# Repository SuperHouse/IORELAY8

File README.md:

I/O Breakout To 8 Relay Drivers
===============================
Copyright 2017-2019 SuperHouse Pty Ltd  
SuperHouse site:  www.superhouse.tv  

Breaks out a 2x6 pin header to 8 low-side MOSFETs suitable for switching
loads such as relays.

Features:

 * Inputs from both a 2x6 shrouded header and separate solder pads

More information is available at:

  http://www.superhouse.tv/iorelay8

INSTALLATION
------------
The design is saved as an EAGLE project. EAGLE PCB design software is
available from www.cadsoftusa.com free for non-commercial use. To use
this project download it and place the directory containing these files
into the "eagle" directory on your computer. Then open EAGLE and
navigate to the project.

DISTRIBUTION
------------
The specific terms of distribution of this project are governed by the
license referenced below.

LICENSE
-------
Licensed under the TAPR Open Hardware License (www.tapr.org/OHL).
The "license" folder within this repository also contains a copy of
this license in plain text format.

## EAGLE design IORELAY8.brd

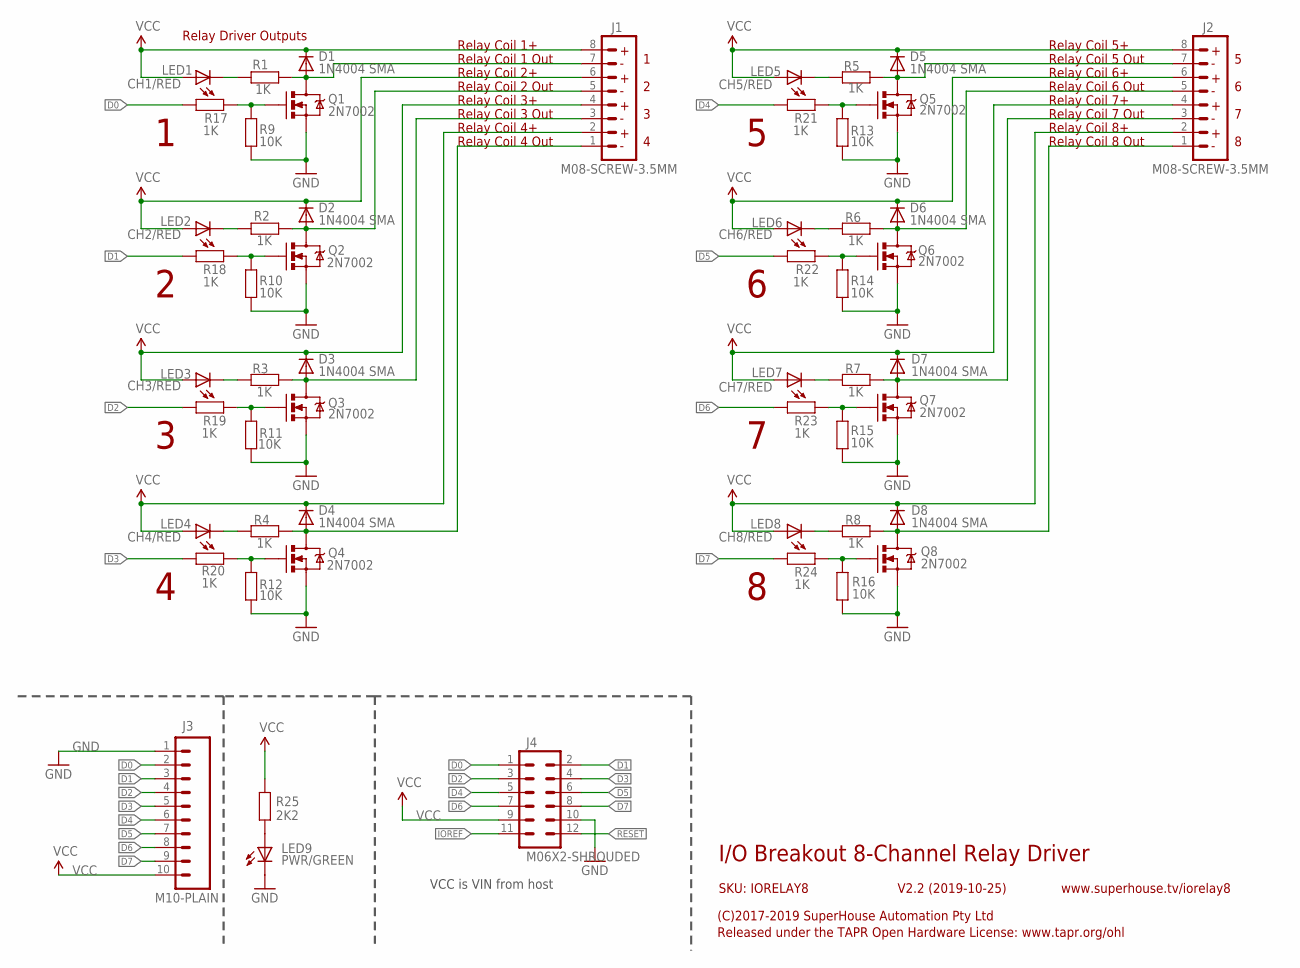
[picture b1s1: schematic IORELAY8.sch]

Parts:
D1, D2, D3, D4, D5, D6, D7, D8: 1N4004 SMA; SMA-DIODE
J1, J2: M08-SCREW-3.5MM; SCREWTERMINAL_3.5MM_8
J3: M10-PLAIN; 1X10
J4: M06X2-SHROUDED; 2X6-SHROUDED
LED1: CH1/RED; LED-0603
LED2: CH2/RED; LED-0603
LED3: CH3/RED; LED-0603
LED4: CH4/RED; LED-0603
LED5: CH5/RED; LED-0603
LED6: CH6/RED; LED-0603
LED7: CH7/RED; LED-0603
LED8: CH8/RED; LED-0603
LED9: PWR/GREEN; LED-0603
Q1, Q2, Q3, Q4, Q5, Q6, Q7, Q8: 2N7002; SOT23-3
R1, R2, R3, R4, R5, R6, R7, R8, R17, R18, R19, R20, R21, R22, R23, R24: 1K; R0603
R9, R10, R11, R12, R13, R14, R15, R16: 10K; R0603
R25: 2K2; R0603

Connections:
D0: J3.2, J4.1, R17.2
D1: J3.3, J4.2, R18.2
D2: J3.4, J4.3, R19.2
D3: J3.5, J4.4, R20.2
D4: J3.6, J4.5, R21.2
D5: J3.7, J4.6, R22.2
D6: J3.8, J4.7, R23.2
D7: J3.9, J4.8, R24.2
GND: J3.1, J4.10, LED9.C, Q1.2 (S), Q2.2 (S), Q3.2 (S), Q4.2 (S), Q5.2 (S), Q6.2 (S), Q7.2 (S), Q8.2 (S), R9.1, R10.1, R11.1, R12.1, R13.1, R14.1, R15.1, R16.1
IOREF: J4.11
unnamed: Q1.1 (G), R9.2, R17.1
unnamed: D2.A, J1.5, Q2.3 (D), R2.2
unnamed: LED9.A, R25.1
unnamed: D1.A, J1.7, Q1.3 (D), R1.2
unnamed: Q2.1 (G), R10.2, R18.1
unnamed: D3.A, J1.3, Q3.3 (D), R3.2
unnamed: Q3.1 (G), R11.2, R19.1
unnamed: D4.A, J1.1, Q4.3 (D), R4.2
unnamed: Q4.1 (G), R12.2, R20.1
unnamed: D5.A, J2.7, Q5.3 (D), R5.2
unnamed: Q5.1 (G), R13.2, R21.1
unnamed: D6.A, J2.5, Q6.3 (D), R6.2
unnamed: Q6.1 (G), R14.2, R22.1
unnamed: D7.A, J2.3, Q7.3 (D), R7.2
unnamed: Q7.1 (G), R15.2, R23.1
unnamed: D8.A, J2.1, Q8.3 (D), R8.2
unnamed: Q8.1 (G), R16.2, R24.1
unnamed: LED2.C, R2.1
unnamed: LED4.C, R4.1
unnamed: LED3.C, R3.1
unnamed: LED1.C, R1.1
unnamed: LED5.C, R5.1
unnamed: LED6.C, R6.1
unnamed: LED7.C, R7.1
unnamed: LED8.C, R8.1
RESET: J4.12
VCC: D1.C, D2.C, D3.C, D4.C, D5.C, D6.C, D7.C, D8.C, J1.2, J1.4, J1.6, J1.8, J2.2, J2.4, J2.6, J2.8, J3.10, J4.9, LED1.A, LED2.A, LED3.A, LED4.A, LED5.A, LED6.A, LED7.A, LED8.A, R25.2

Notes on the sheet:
I/O Breakout 8-Channel Relay Driver
V2.2 (2019-10-25)
SKU: IORELAY8
(C)2017-2019 SuperHouse Automation Pty Ltd
Released under the TAPR Open Hardware License: www.tapr.org/ohl
www.superhouse.tv/iorelay8
Relay Coil 1 Out
Relay Coil 1+
Relay Coil 2+
Relay Coil 3+
Relay Coil 4+
Relay Coil 4 Out
Relay Coil 3 Out
Relay Coil 2 Out
Relay Coil 8 Out
Relay Coil 8+
Relay Coil 5+
Relay Coil 5 Out
Relay Coil 6+
Relay Coil 6 Out
Relay Coil 7+
Relay Coil 7 Out
Relay Driver Outputs
VCC is VIN from host

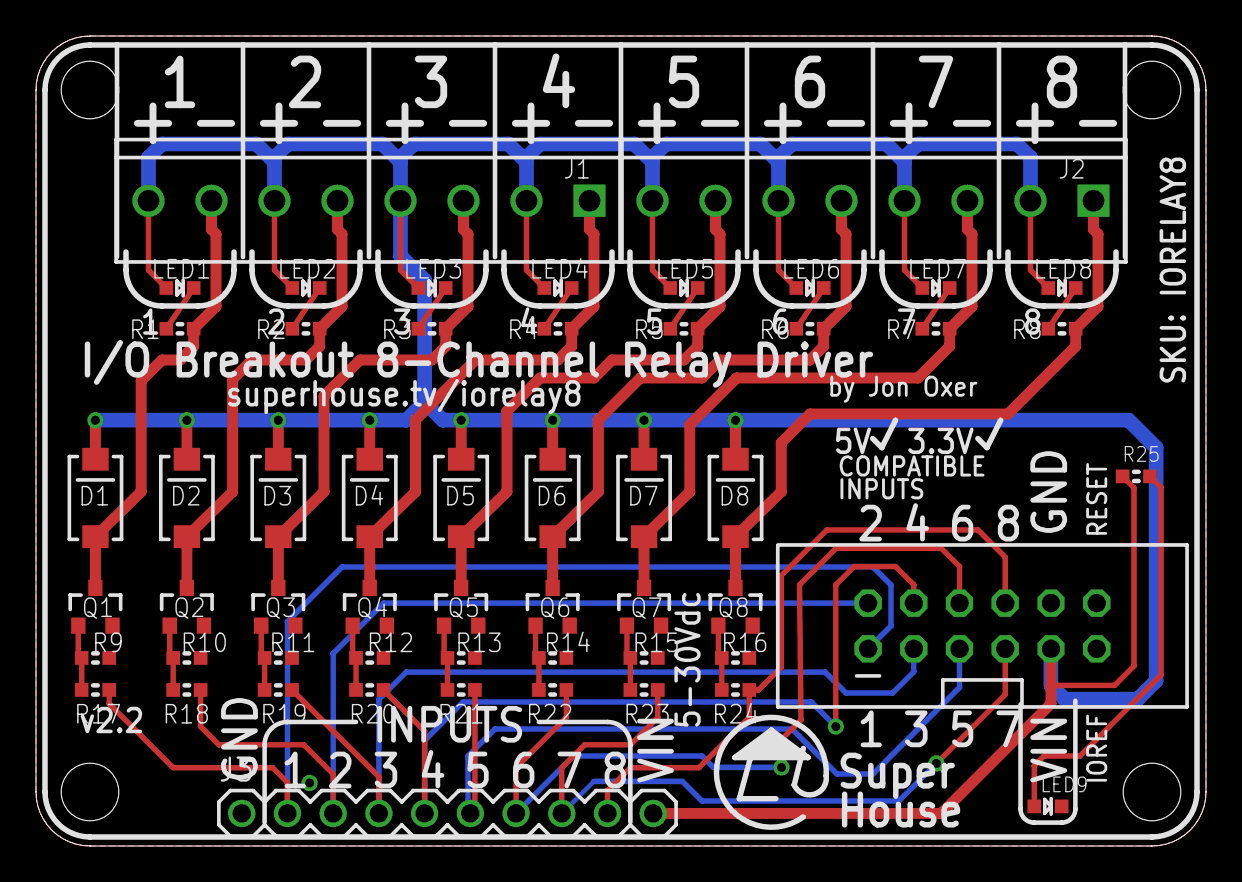
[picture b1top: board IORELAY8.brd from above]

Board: 2 copper layers, 65.0 x 45.0 mm, 55 parts (1 on the bottom side), 35 nets.

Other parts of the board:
U$6: OSHW_10X200_NOTEXT

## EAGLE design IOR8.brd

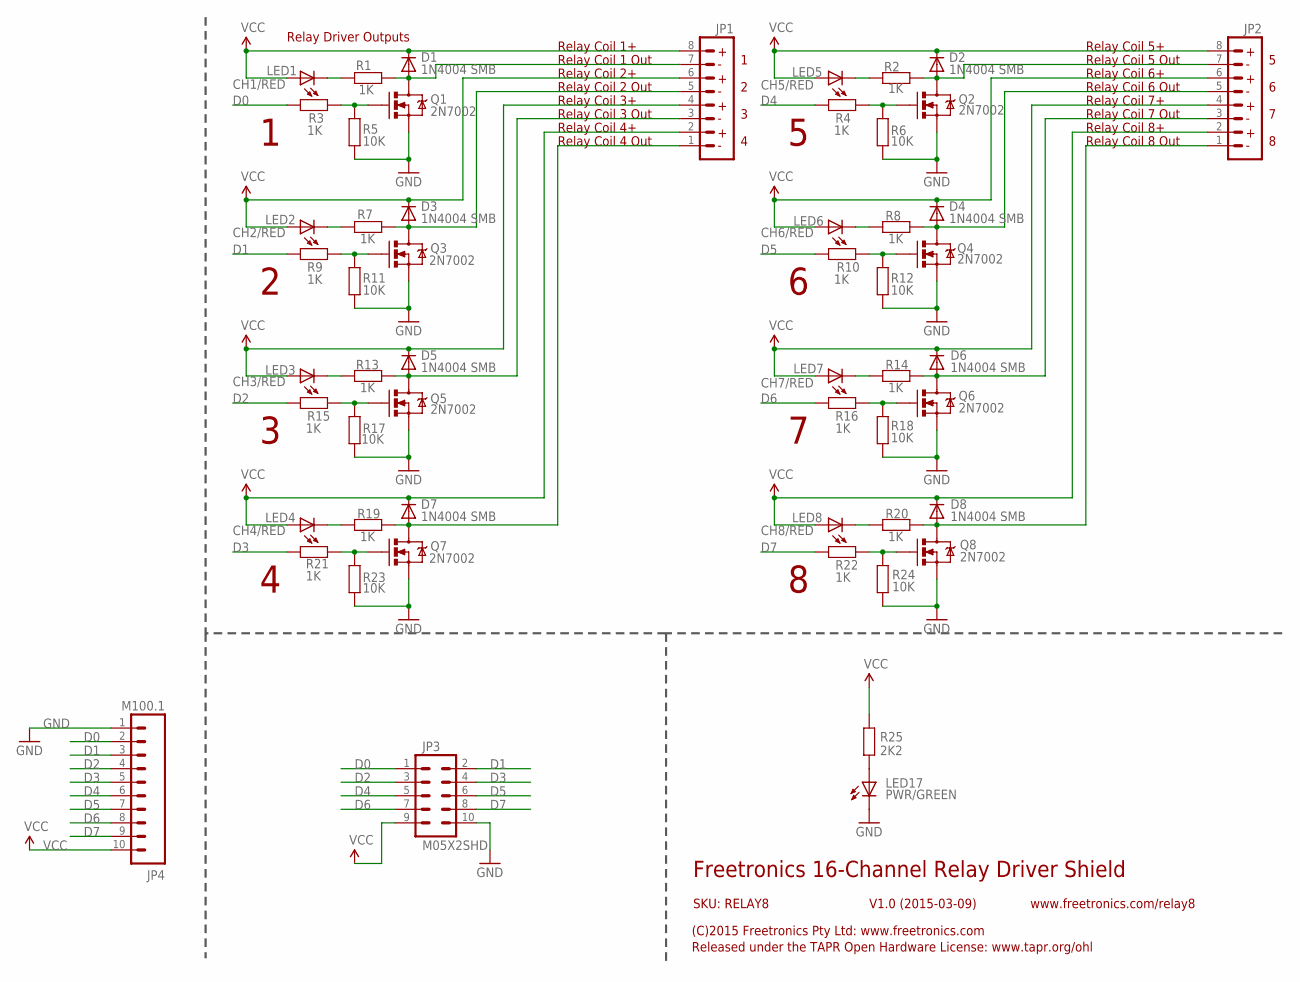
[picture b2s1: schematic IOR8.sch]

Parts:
D1, D2, D3, D4, D5, D6, D7, D8: 1N4004 SMB; SMB-DIODE
JP1, JP2: M08; TERMINALBLOCK_3.5MM_8
JP3: M05X2SHD; 2X5-SHROUDED
JP4: M100.1; 1X10
LED1: CH1/RED; LED-0603
LED2: CH2/RED; LED-0603
LED3: CH3/RED; LED-0603
LED4: CH4/RED; LED-0603
LED5: CH5/RED; LED-0603
LED6: CH6/RED; LED-0603
LED7: CH7/RED; LED-0603
LED8: CH8/RED; LED-0603
LED17: PWR/GREEN; LED-0603
Q1, Q2, Q3, Q4, Q5, Q6, Q7, Q8: 2N7002; SOT23-3
R1, R2, R3, R4, R7, R8, R9, R10, R13, R14, R15, R16, R19, R20, R21, R22: 1K; 0603
R5, R6, R11, R12, R17, R18, R23, R24: 10K; 0603
R25: 2K2; 0603

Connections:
D0: JP3.1, JP4.2, R3.2
D1: JP3.2, JP4.3, R9.2
D2: JP3.3, JP4.4, R15.2
D3: JP3.4, JP4.5, R21.2
D4: JP3.5, JP4.6, R4.2
D5: JP3.6, JP4.7, R10.2
D6: JP3.7, JP4.8, R16.2
D7: JP3.8, JP4.9, R22.2
GND: JP3.10, JP4.1, LED17.C, Q1.2 (S), Q2.2 (S), Q3.2 (S), Q4.2 (S), Q5.2 (S), Q6.2 (S), Q7.2 (S), Q8.2 (S), R5.1, R6.1, R11.1, R12.1, R17.1, R18.1, R23.1, R24.1
unnamed: Q1.1 (G), R3.1, R5.2
unnamed: D3.A, JP1.5, Q3.3 (D), R7.2
unnamed: LED17.A, R25.1
unnamed: D1.A, JP1.7, Q1.3 (D), R1.2
unnamed: Q3.1 (G), R9.1, R11.2
unnamed: D5.A, JP1.3, Q5.3 (D), R13.2
unnamed: Q5.1 (G), R15.1, R17.2
unnamed: D7.A, JP1.1, Q7.3 (D), R19.2
unnamed: Q7.1 (G), R21.1, R23.2
unnamed: D2.A, JP2.7, Q2.3 (D), R2.2
unnamed: Q2.1 (G), R4.1, R6.2
unnamed: D4.A, JP2.5, Q4.3 (D), R8.2
unnamed: Q4.1 (G), R10.1, R12.2
unnamed: D6.A, JP2.3, Q6.3 (D), R14.2
unnamed: Q6.1 (G), R16.1, R18.2
unnamed: D8.A, JP2.1, Q8.3 (D), R20.2
unnamed: Q8.1 (G), R22.1, R24.2
unnamed: LED2.C, R7.1
unnamed: LED4.C, R19.1
unnamed: LED3.C, R13.1
unnamed: LED1.C, R1.1
unnamed: LED5.C, R2.1
unnamed: LED6.C, R8.1
unnamed: LED7.C, R14.1
unnamed: LED8.C, R20.1
VCC: D1.C, D2.C, D3.C, D4.C, D5.C, D6.C, D7.C, D8.C, JP1.2, JP1.4, JP1.6, JP1.8, JP2.2, JP2.4, JP2.6, JP2.8, JP3.9, JP4.10, LED1.A, LED2.A, LED3.A, LED4.A, LED5.A, LED6.A, LED7.A, LED8.A, R25.2

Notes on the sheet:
Freetronics 16-Channel Relay Driver Shield
V1.0 (2015-03-09)
SKU: RELAY8
(C)2015 Freetronics Pty Ltd: www.freetronics.com
Released under the TAPR Open Hardware License: www.tapr.org/ohl
www.freetronics.com/relay8
Relay Coil 1 Out
Relay Coil 1+
Relay Coil 2+
Relay Coil 3+
Relay Coil 4+
Relay Coil 4 Out
Relay Coil 3 Out
Relay Coil 2 Out
Relay Coil 8 Out
Relay Coil 8+
Relay Coil 5+
Relay Coil 5 Out
Relay Coil 6+
Relay Coil 6 Out
Relay Coil 7+
Relay Coil 7 Out
Relay Driver Outputs

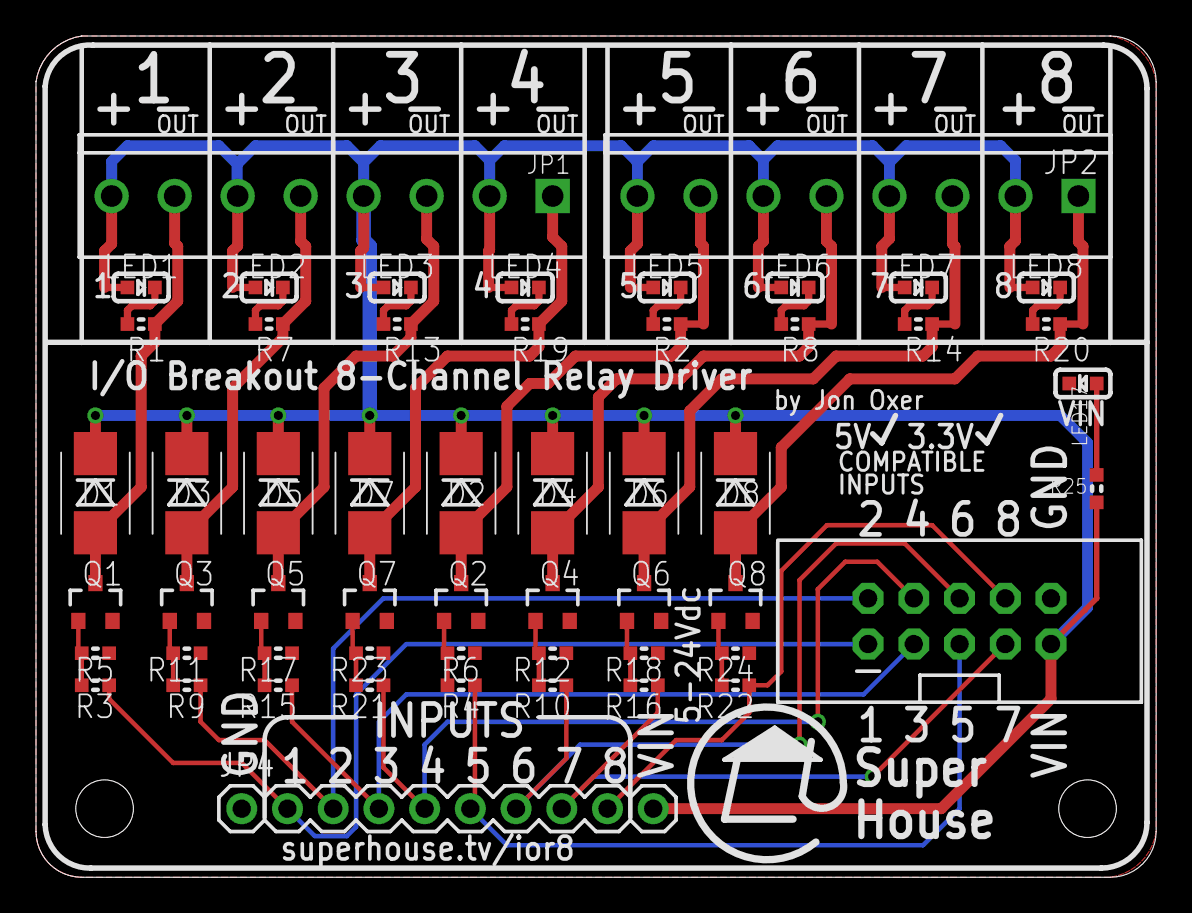
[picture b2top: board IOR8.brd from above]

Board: 2 copper layers, 62.2 x 46.7 mm, 55 parts (1 on the bottom side), 35 nets.

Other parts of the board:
U$6: OSHW_10X200_NOTEXT

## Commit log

2017-07-21 Initial project import for possible v1.0 release
2017-07-24 Expanded headers to 2x6 to include IOREF and RESET for v2.0 release
2017-07-24 Renamed project files
2017-07-24 Updated README to match extended headers and new URL
2017-07-25 Resized board on metric grid
2017-08-03 Improved position of part designators
2019-07-01 Replaced most parts using SuperHouse library to add 3D models
2019-07-18 Replaced parts using SuperHouse libraries to add 3D models
2019-10-25 Silkscreen change for v2.2 release
2019-10-25 Scaled render
2019-10-27 DRC, designator, and value cleanups for v2.2 release

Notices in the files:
IOR8.brd:
(c) 2017 SuperHouse Pty Ltd
Hardware License: tapr.org/OHL
parts and their libraries:
freetronics-original: Licensing: CC v3.0 Share-Alike You are welcome to use this library for commercial purposes.
